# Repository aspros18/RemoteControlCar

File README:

Git URL: https://github.com/fzoli/RemoteControlCar

Bevezetés
---------

A projekt célja egy távirányítós autó vezérlése interneten át.

Az autó vezérlése Android operációs rendszerrel futó mobiltelefon segítségével valósul meg.

A telefon felhasznált eszközkészlete:
- hátsó kamera, ami segítségével lehet látni, mi van az autó előtt
- giroszkóp, ami segítségével meg lehet tudni a gyorsulás és kanyarodás mértékét valamint az út lejtését (ha nincs fék az autón, az emelkedő/lejtő adat alapján megoldható, hogy egy helyben álljon az autó bármikor, ha azt akarjuk)
- GPS vevőt, ami segítségével megbecsülhető a pillanatnyi sebesség és megtudható a kellően pontos tartózkodási hely
- USB port, ami segítségével - egy SparkFun által gyártott mikrovezérlő - az IOIO for Android (DEV-10748) köthető össze a telefonnal. A mikrovezérlőhöz tartozik egy Java nyelvre írt API, ami segítségével ADB (Android Debug Bridge) vagy ADK (Accessory Development Kit) kapcsolaton keresztül a telefon képes kommunikálni a külvilággal. Az API automatikusan kapcsolódik az eszközhöz, nem fontos, melyik kapcsolaton keresztül, de az ADB van előnyben részesítve.
- mobilhálózat, ami segítségével HSPA vagy 3G mobilinternetet használva elküldhető a videó jel, a statisztika és foghatóak a vezérlő jelek
- mobilakku, ami ellátja a mobiltelefont árammal. Azt is jó látni interneten keresztül, hány %-on áll az aksi.

A mikrovezérlő célja:
- vezérelni az autót a telefonnal
- az autó akkumulátorának töltöttségi szintjének megszerzése

Egyéb eszközök:
- kézzel állítható, kétállású kapcsoló, ami eldönti, hogy a beépített mikrovezérlő (ami a gyári távirányító jelének segítségével vezérli az autót) vagy a telefon mikrovezérlője (ami az internetről kapott utasításokkal vezérli az autót) legyen aktív. Erre azért van szükség, hogy ne történhessen meg az, hogy mindkét mikrovezérlő egyazon időben jelzést adjon le és túlfeszültséget okozzon az autó áramkörében
- a lista még bővülni fog olyan dolgokkal mint pl. ellenállás

A hálózati kommunikáció terve:
------------------------------

A kommunikáció SSL titkosítást használva socketek segítségével történik.
A tanúsítványokban szereplő CN (Common Name) mező alapján történik a felhasználó számítógépek és emberek azonosítása, tehát nincsenek felhasználónevek és jelszavak.
Az összes tanúsítvány egyetlen kiállítótól (CA) származik és mind a socket szerver, mind a socket kliensek csakis ebben az egy kiállítóban bízik meg.
Ez azt eredményezi, hogy az összes olyan tanúsítványt elfogadják, amiket a konkrét CA állított ki, de az összes többit elutasítják.

Az SSL többféle próbának is aláveti a socketeket mielőtt létrejönne a kapcsolat:
- megnézi, hogy megbízható-e a tanúsítvány (vagyis inkább a CA)
- megnézi, hogy nem járt-e le a tanúsítvány
- ellenőrzi a hostnevet

A hostnév-ellenőrzés ki van kapcsolva, mert a szabvány szerint a szerver hostnevének és a tanúsítványában szereplő CA mezőnek meg kell egyeznie.
Fentebb írtam, hogy a CA mezőt én a felhasználók azonosítására használom (amolyan felhasználónév szerűség), másrészt a szervernek nem feltétlenül van hostneve vagy a hostnév változó (Pl. IP cím alapján is lehet szerverhez kapcsolódni).

Az egyszerűsített kapcsolati ábra:
Host <-> Bridge <*> Controller

Jelmagyarázat:
<-> egy-egy kapcsolat
<*> egy-sok kapcsolat
Host: a mobiltelefon által indított kliens socket (magyarban is host)
Bridge: egy olyan socket szerver, ami kliens socketek kapcsolódására vár (magyarra fordítva: híd)
Controller: azok a kliens programok, amik segítségével vezérelhető az autó (magyarra fordítva: vezérlő)

Host:
-----

Socket oldalról megközelítve:
A host az én esetemben egy mobiltelefon, ami legtöbbször mobilinternetet - ritkábban Wi-Fi hálózatot és akkor belső IP alapján is lehet címezni - használ  arra, hogy fel tudja venni a kapcsolatot a híddal. Socket szempontjából ő kliens szerepet tölt be. Ennek az az oka, hogy az összes internetes IPv4 cím ki lett már osztva és az internetszolgáltatók minden trükköt bevetnek, hogy ki tudják szolgálni az összes internetet használni akaró gépet. A mobilszolgáltatók ezért NAT-olt IP címet osztanak ki a mobilinternetet használó gépeknek. Ezzel a trükkel egy internetes IP cím (rövidebben WAN IP) több géphez is tartozhat, tehát több gépet ki lehet szolgálni, de van egy hátránya is - amiről a mobilinternetezők nagy része nem is tud - mégpedig az, hogy nincs egy elérhető aktív port sem. Mivel nincs aktív port, hiába üzemeltetünk szervert a telefonon, azt az internetről nem lehet elérni, vagyis csak kliens szerep lehetséges.

A kamera elérése:
A telefon kamerájának képkockái MJPEG streameléssel jutnak el a hídhoz.
Eredeti elképzelésem szerint saját magam olvastam volna a kamera képét és küldtem volna a socket servernek.
A probléma ott kezdődött, hogy az android API nem éppen programozóbarát ha médiáról van szó.
Egyrészt csak akkor hajlandó képkockákat adni, ha azt felületen is megjelenítem (és ennek nem sok értelme van) valamint az eseménykezelőben egy bájt tömböt kapok, amiben YUV formátumú kép van. Ezzel még nem is lenne gond, mert ha valakinek csak a fekete-fehér tartomány kell, akkor még örül is neki, de ha színes képet szeretne az én telefonom kb. 800 ezredmásodpercig dolgozik rajta és akkor még nem is méreteztem át, nem is tömörítettem JPEG formátumba. Olyan 0.7 FPS érhető el így összességében. Gondoltam utánanézek már kész androidos programoknak, amik tudnak videót streamelni. A sok androidos program közül egy megfelelően működőt találtam is, aminek a neve IP Webcam. Java csomag alapján keresve "com.pas.webcam". Ez volt az egyetlen olyan program, ami már megfelelő FPS-t tudott és nem észleltem késést sem. Meg is néztem az okát (hogy hogyan, az már más kérdés). Natív kódot használtak fel, amit C nyelven írtak meg. (Az Android is támogatja a natív kódokat. Bővebben: NDK - Native Development Kit)
Az IP Webcam program HTTP szervert használ és lehetőség van felhasználónév és jelszó beállítására, valamint megadhatjuk a szerver portját, a JPEG képek paramétereit (felbontás, FPS, képminőség) és hogy induljon-e el a telefon indulásakor a program, hogy bármikor hozzá lehessen férni a kamerához.

A telefonon futó program terve:
A telefonon egy Android service fog futni, amit egy egyszerű Activity felületről lehet majd elindítani ill. leállítani.
A service ha leállítódik valami ok miatt (pl. kevés a memória), úgy lesz beállítva, hogy amint lehetséges, induljon el.
Ha a telefon újraindulna miközben a service fut (pl. SD kártyáról fut vagy 100 program és szegény kártya nem bírja olyan gyorsan adni az adatokat mint kéne), a service az OS (operációs rendszer rövidítése) felállása után szintén elindul.
A service az elindulása után azonnal kapcsolódni próbál a hídhoz, ha nem sikerül percenként próbálkozik.
Ha a kapcsolat megszakad, azonnal elindul a kapcsolódás folyamata.
Ezzel minden nem várt hibára megtörtént az óvintézkedés.
A service elindulásakor, ha nem fut az IP Webcam program, akkor az API-ja segítségével a service elindítja azt. (Az ip-webcam könyvtárban további infó.)
A service elindítása előtt a felületen a menüből kezdeményezhető további beállítás.
Itt kell megadni:
- a híd címét (host vagy IP) és portját (amin a socket servlet figyel)
- a tanúsítvány publikus kulcsát (crt fájl) és privát kulcsát (key fájl), amivel a hídhoz kapcsolódik és titkosít.
- a tanúsítvány kiállítójának publikus kulcsát
- mennyi időközönként küldjön statisztikát a telefon
Opcionális beállításként megadható a híd tanúsítványának CN mezője, csak a biztonság kedvéért.
Előfordulhat, hogy rossz címet állítottunk be és nem a híd van címezve. Ez esetben ha a CN mező meg van adva, kiküszöbölhető a fölösleges kapcsolódás és azonnal egyértelmű hibajelzést kapunk. Ha nincs megadva a CN mező, a program percenként fölöslegesen fog próbálkozni, konkrét hibát nem jelezve.

A hang stream, eredetileg kikapcsolt és kérhető lesz bekapcsolásra. Kikapcsolása esetén elég a socket streamet lezárni és kezelni kell a kivételt.
A streamet az android beépített szolgáltatása (MediaRecorder.AudioEncoder.AAC) fogja szolgáltatni és a híd fogja tovább adni a vezérlőknek.

Bridge:
-------

A hídnak két szerepköre van:
- vár a hostra - amitől a videót és a statisztikát kapja és akinek a vezérlőjelet küldi majd
- kiszolgálja a vezérlőket - amik irányítani szeretnék az autót - és eldönti, hogy ki vezérelheti az autót, ha több kérés van egy időben

Úgy terveztem meg a socket alapú kommunikációkat, hogy a híd el tudja dönteni, mi célja lesz a kapcsolatnak és egy időben több kapcsolatot kezelhessen.
A híd esetén a host CN mezőjét kötelező megadni, mert a híd ez alapján tudja, hogy a socket kliens vezérlő-e vagy host. EZ NAGYON FONTOS!!!
A híd esetében megadható több CN mező is, amik segítségével lehet tudni, mely tanúsítványok lesznek a hostok ha esetleg több autó is távvezérelt lesz a jövőben. (Meg lehetett volna oldani úgy is, hogy a socket kliensek még a kapcsolatazonosító kérése előtt közölték volna, hogy ők hostok vagy vezérlők, de ez esetben a híd nem tudna pontos listát adni a hostokról.)

[Opcionális terv: A híd mellé lehetne egy webszervert is tenni. Regisztrálhatnának internetről mások, akiknek el lett adva egy ilyen autó és van hozzá mobiltelefonjuk. A webszerver is SSL-t használna az alapértelmezett 443-as porttal. Itt akár tanúsítványt is generáltathatnának (hostjukhoz és vezérlőjeikhez) így a híd socket servere megbízhatónak találná őket és szintén tudná ki a host és ki a vezérlő. A híd szolgáltatása havidíjas is lehetne és azoknak lenne jó, akik nem szeretnének saját híd szervert üzemeltetni. A host mikrovezérlő kódját ez esetben úgy kellene megtervezni, hogy interface alapú legyen és a felületről több autó típust lehessen választani az implementált osztályok alapján. Szép álom lenne, ha a mobilinternetes szolgáltatókkal meg lehetne egyezni, hogy ne mérjék a forgalmat és kapnak a bevételből :-) ]

Host felőli kapcsolatok:
1. MJPEG stream: hídnak letöltés, hostnak feltöltés
2. Statisztika adatok: objektumos stream, hídnak letöltés, hostnak feltöltés
3. Vezérlő parancsok a hídtól (az autónak és a telefonon futó programnak): objektumos stream, hídnak feltöltés, hostnak letöltés

Vezérlő felőli kapcsolatok:
1. MJPEG stream: hídnak feltöltés, vezérlőnek letöltés
2. Statisztika adatok (a hostról és a hídról): objektumos stream, hídnak feltöltés, vezérlőnek letöltés
3. Vezérlő parancsok a vezérlőtől (a hostnak és a hídnak): objektumos stream, hídnak letöltés, vezérlőnek feltöltés

Bővebb magyarázat:
- A kapcsolatok előtt a számozás kapcsolatazonosítót és prioritási sorrendet is jelent.
- A híd a hostnak főként autóvezérlő utasításokat közöl (a 3-mas kapcsolaton át), de a telefonnak közölheti azt is,
  hogy hagyja abba az MJPEG streamelést vagy éppen kezdje el.
- A vezérlő a hídnak főként autóvezérlő utasításokat ad, de üzenhet a hídnak is, hogy szeretné átvenni az autó irányítását.
- A híd is üzenhet a vezérlőnek, ha éppen elvették tőle az irányítást, jelezze a felületen.

A kapcsolat kialakítása a következő módon valósul meg:
A kliens három kapcsolatot alakít ki ugyan azzal a sockettel, a kapcsolat létrejötte után új szálban kezdődik meg a feldolgozás.
A szerver amíg aktívan fut (tehát a Socket server nincs bezárva) cikluson belül mindig várja a klienseket és ha létrejön egy SSLSocket, ő is külön szálban dolgozik vele tovább, hogy képes legyen több kapcsolatot kiszolgálni egy időben.

A kapcsolat kialakításának lépései: (Szerver alatt a híd socket szerverét értem.)
0. A kliens socket kapcsolódik a szerver sockethez és sikerül az SSL kézfogás, létrejön a kapcsolat és mindkét oldalon egy SSLSocket objektum.
1. a) A szerver a kliens-tanúsítvány CN mezejének alapján megtudja, hogy a kliens host vagy vezérlő és hogy pontosan kivel is van dolga.
   b) A szerver megnézi, hogy az adott szerepkörben az adott névhez hány kapcsolat van már kialakítva.
   c) A szerver inkrementálja a B pontban kapott számot és így megkapja az aktuális kapcsolat azonosítóját
      és a fenti felsorolás alapján már tudja is, mire lesz használva a kapcsolat.
2. A szerver elküldi a kliensnek a kapcsolatazonosítót. Másképp fogalmazva: A kliens lekéri a kapcsolatazonosítót.
3. Mindkét oldal a kapcsolatazonosító alapján együttműködve kezeli a kapcsolatot.
4. Bármelyik oldal lezárhatja a kapcsolatot, ha úgy dönt. Ekkor befejeződik a kommunikáció.

Ha a hídra ugyan azzal a tanúsítvánnyal kapcsolódnak több helyről, a híd a régebbi kapcsolatokat bezárja.
Így ki van kerülve az, hogy két helyről vezérelhessék az autót ellentmondásos üzenetet leadva mint pl. menj jobbra és balra is.

Jogkezelés:
Előfordulhat olyan eset, hogy egy autót több vezérlő is szeretne irányítani.
Erre azt találtam ki, hogy csinálok a hídra egy tanúsítvány-prioritás listát.
A nagyobb prioritású vezérlő bármikor elveheti a vezérlést a kisebb prioritású vezérlőktől, de egyébként minden vezérlő kapcsolódhat a hídhoz és minden
információt láthat, csak a vezérléstől vannak megfosztva.
Amint felszabadul a vezérlés, bárki kérheti az autó vezérlését prioritástól függetlenül és meg is kapja.
(Kérni lehet akkor is, ha éppen vezérlik az autót, de az csak kérvényt jelent, semmi többet. Amint felszabadul a vezérlés az első kérvényt benyújtó meg is kapja.)
(Ha a prioritáslistában egyetlen név szerepel, akkor úgy fog funkcionálni, mint ha root lenne, mivel mindenki felett áll ez esetben.)
Ha nagyobb prioritású kapcsolódik a hídhoz, mint aki vezérli az autót, addig amíg nem kéri a vezérlést, nem veszi el a híd az aktuális vezérlőtől az irányítást.
Aki nem szerepel a prioritáslistában, az olyan, mint ha a legutolsó utolsó helyen szerepelne a listában és a többi - listában nem szereplő - felhasználóval egyenrangúnak számít, tehát ők egymástól nem tudják elvenni a vezérlést.
Ha a vezérlő sokáig nem cselekszik, tehát nincs a gép előtt, a vezérlést elveszi a híd tőle.

Internet sávszélesség:
A híd létrejöttének fő célja az volt, hogy egyetlen egy kapcsolat (ami valójában három socket kapcsolat) legyen a mobilinternet oldaláról és az is takarékos legyen mivel forgalom- és sebességkorlátos az internet.
A hídba be van téve egy olyan sávszélesség csökkentő funkció is, hogy csak akkor kéri az MJPEG streamet a hosttól, ha van legalább egy vezérlő kapcsolódva hozzá.

Konfig fájl:
A híd esetén is meg kell adni a tanúsítvány publikus és titkos kulcsának az elérhetőségét és a kiállító publikus kulcsának az elérhetőségét.
A tanúsítvány prioritásokat és a hostlistát is itt kell megadni, de ha bevezetésre kerül egy webes felület, átkerülnek egy közös adatbázisba.

Controller:
-----------

A vezérlő az a program, ami megjeleníti az autó adatait és ha van lehetősége vezérli az autót.
Ez egy PC-n futó java alapú desktop alkalmazás lényegében, ami szintén a hídhoz kapcsolódik socket kliensként.
A felületen lehetőség van - és kötelező is első induláskor - beállítani a híd címét és portját valamint a tanúsítvány publikus és titkos kulcsát és a kiállító publikus kulcsát.
A kiállító kulcsára azért van szükség mert kliens oldalon is ellenőrizve van a szerver tanúsítvány megbízhatósága, nem csak szerver oldalon, hogy a man-in-middle támadás lehetetlen legyen.
A vezérlés billentyűzet és egér segítségével történik.
Az egérrel pontos utasítást lehet adni mind sebesség, mind irány terén.
A billentyűzettel egyszerűbb, de durvább irányítást érhet el a felhasználó és több vezérlés mód közül választhat.
(A vezérlési módok a durvaságot szabályozzák pl. előre nyílra egyenletesen gyorsuljon fel vagy földkaparással max grafttal induljon el)

Egy kis trükk:
--------------

Egyes mobilszolgáltatók csomagjaiban a webböngészés nem számít bele a forgalomkorlátba.

Ez esetben socketek helyett mondjuk Tomcat webszervert lehetne használni.
- A terv lényege ugyan az, csak a kapcsolatazonosítók helyett HTTP címzés lenne használva.
- Az MJPEG stream HTTP POST-tal streamelhető a hídnak - ami a Tomcat webszerver.
- A vezérlő utasítások JSON-nal objektummá alakíthatók Stringből és objektumból Stringre, és a HTTP tartalom is gond nélkül használható streamelés céljára.

Továbbfejlesztés
----------------

További két socket kapcsolat segítségével megoldható lenne, hogy a telefon mikrofonjából megkapjuk a hangot is a kép mellé és a vezérlő számítógép mikrofonjából meg a telefonon játsszunk le hangot.
A telefonból érkező hang stream ki/be kapcsolható lenne, alapértelmezetten ki lenne kapcsolva takarékosság miatt.
Az autót vezérlő kliens tudná csak ki/be kapcsolni a streamet és csakis ő tudna hang streamet küldeni a telefonnak.
A sávszélesség kímélése érdekében a Javara írt Tritonus API-t használva lehetne tömöríteni GSM vagy MP3 formátumba a monó 16 bites PCM-ről. (Mondjuk GSMFormatConversionProvider segítségével.)
Egyéb pluginok: http://www.tritonus.org/plugins.html
Példa: http://www.jsresources.org/examples/GSMEncoder.java.html
Ha a Tritonus még sem használható út, marad a GZipInputStream és társa a GZipOutputStream.
Vagy egy másik út: http://www.jsresources.org/apps/9159_TimeTurner.pdf

Az autón lévő tartó, amiben a mobil lesz, lehetne motor által vezérelhető, hogy a kereszteződéseket be lehessen látni és igény szerint hátra is lehessen tekinteni.
A giroszkóp adatait a telefon programja csak az alapállásban adná le a megbízhatóság miatt. (Vagy ha szükség van rá, akkor csak a motor mozgása közben lenne inaktív és az algoritmus meg lenne írva úgy, hogy több helyzetből is jó adatokat közöljön.)

A telefont tartó eszköz lehetőleg védje a telefont a külső támadások ellen és az eső ellen, kulccsal zárható legyen.
Ha ez meg lett oldva, a kábeleket is jó lenne biztonságosan elvezetni szintén védve és a kapcsolót, ami átkapcsolhat internetes vezérlésről, azt is a kulccsal
zárt, védett helyen belülre kéne elhelyezni.

Nem ártana egy közös chat funkció se. Nem kellene tárolni az üzeneteket, ebből kifolyólag nem lenne offline üzenetküldés.
Csak annyi célja lenne, hogy az autót vezérlő felhasználók tudjanak beszélgetni egymással.

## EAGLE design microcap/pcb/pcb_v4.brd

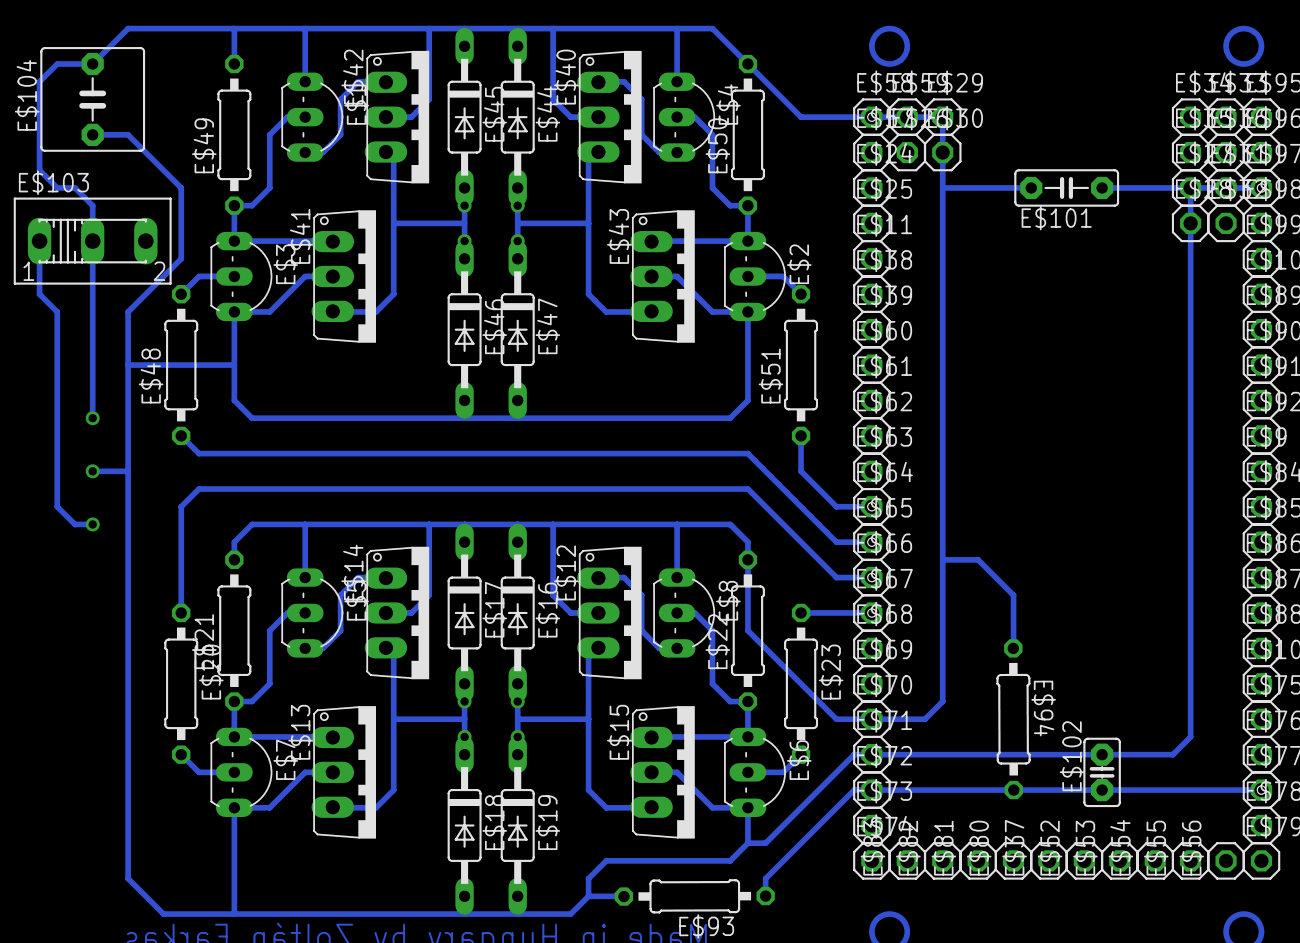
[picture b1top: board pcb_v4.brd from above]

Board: 2 copper layers, 104 parts (0 on the bottom side), 18 nets.

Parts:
E$1, E$2, E$3, E$4, E$5, E$6, E$7, E$8: TO92-CBE
E$9, E$10, E$11, E$24, E$25, E$26, E$27, E$28, E$29, E$30, E$31, E$32, E$33, E$34, E$35, E$36, E$37, E$38, E$39, E$52, E$53, E$54, E$55, E$56, E$57, E$58, E$59, E$60, E$61, E$62, E$63, E$64, E$65, E$66, E$67, E$68, E$69, E$70, E$71, E$72, E$73, E$74, E$75, E$76, E$77, E$78, E$79, E$80, E$81, E$82, E$83, E$84, E$85, E$86, E$87, E$88, E$89, E$90, E$91, E$92, E$95, E$96, E$97, E$98, E$99, E$100: 1X01
E$12, E$13, E$14, E$15, E$40, E$41, E$42, E$43: T-30_V
E$16, E$17, E$18, E$19, E$44, E$45, E$46, E$47: C2992
E$20, E$21, E$22, E$23, E$48, E$49, E$50, E$51, E$93, E$94: 0207/10
E$101: C5B2.5
E$102: C2.5-2
E$103: 255SB
E$104: C5B7.2

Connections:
S$2: E$2.C, E$4.B, E$50.1
S$5: E$3.B, E$48.2
S$6: E$2.B, E$51.2
S$7: E$5.B, E$7.C, E$21.1
S$8: E$45.A, E$46.C
S$9: E$1.B, E$3.C, E$49.1
S$12: E$17.A, E$18.C
S$15: E$23.1, E$67.1
S$16: E$6.C, E$8.B, E$22.1
S$17: E$6.B, E$23.2
S$18: E$51.1, E$64.1
S$19: E$16.A, E$19.C
S$21: E$7.B, E$20.2
S$22: E$44.A, E$47.C
S$23: E$48.1, E$65.1
S$28: E$1.C, E$4.C, E$5.C, E$8.C, E$16.C, E$17.C, E$21.2, E$22.2, E$29.1, E$44.C, E$45.C, E$49.2, E$50.2, E$58.1, E$59.1, E$70.1, E$101.2, E$103.2, E$104.2
S$29: E$2.E, E$3.E, E$6.E, E$7.E, E$18.A, E$19.A, E$46.A, E$47.A, E$71.1, E$97.1, E$101.1, E$104.1
S$36: E$20.1, E$66.1

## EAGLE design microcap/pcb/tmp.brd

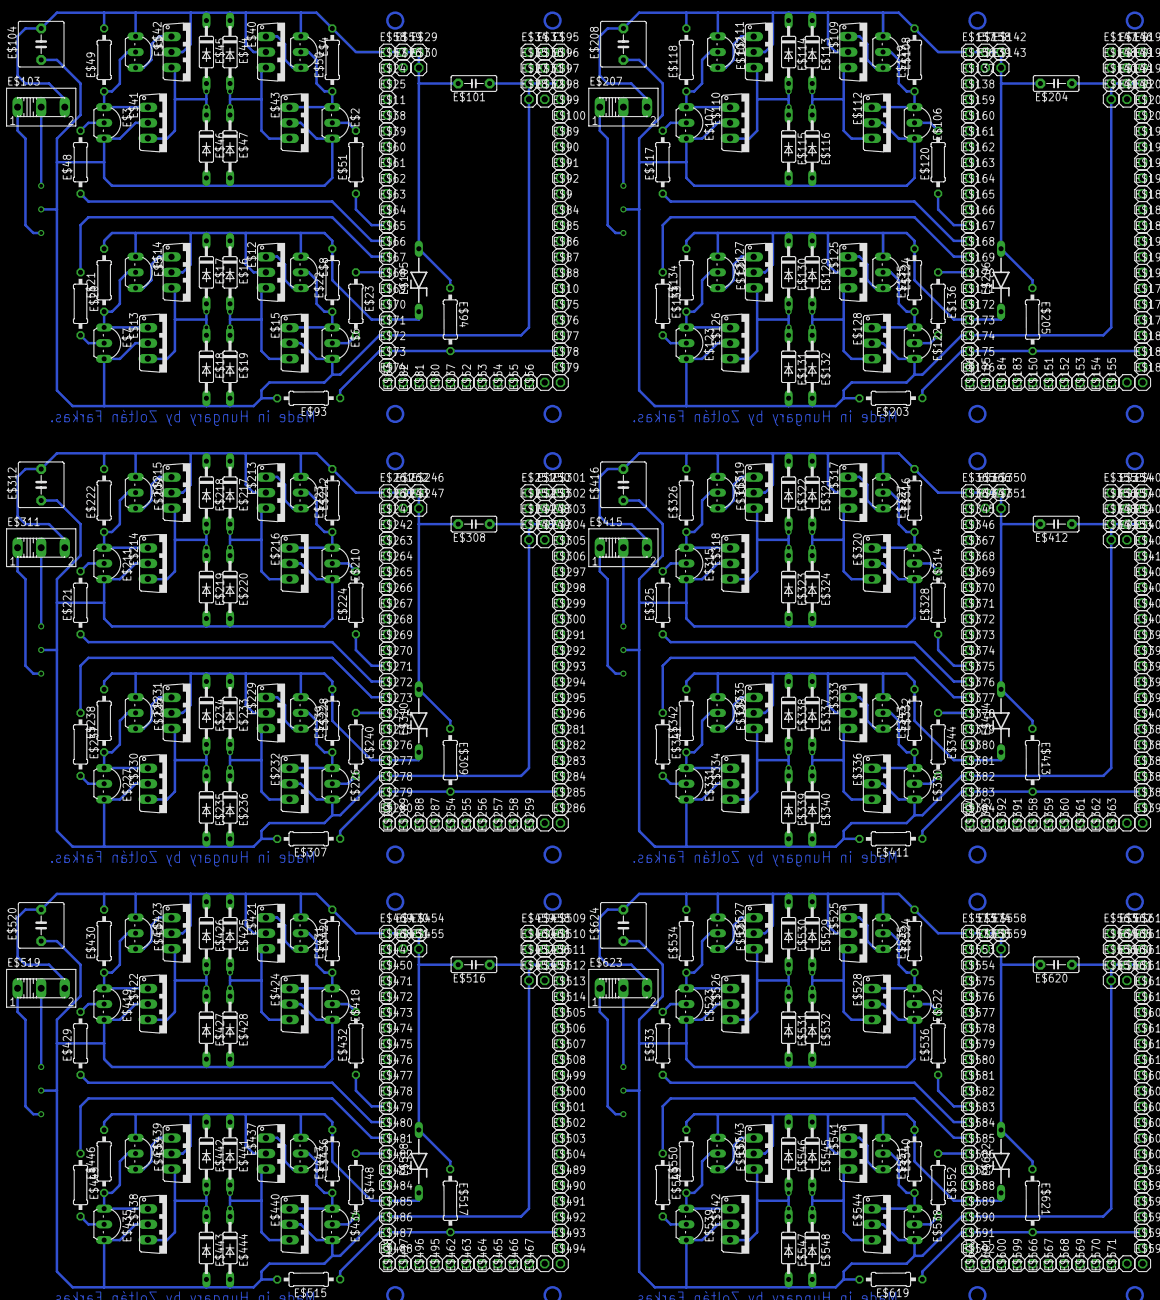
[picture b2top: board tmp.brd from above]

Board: 2 copper layers, 624 parts (0 on the bottom side), 114 nets.

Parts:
E$1, E$2, E$3, E$4, E$5, E$6, E$7, E$8, E$102, E$106, E$107, E$108, E$121, E$122, E$123, E$124, E$209, E$210, E$211, E$212, E$225, E$226, E$227, E$228, E$313, E$314, E$315, E$316, E$329, E$330, E$331, E$332, E$417, E$418, E$419, E$420, E$433, E$434, E$435, E$436, E$521, E$522, E$523, E$524, E$537, E$538, E$539, E$540: TO92-CBE
E$9, E$10, E$11, E$24, E$25, E$26, E$27, E$28, E$29, E$30, E$31, E$32, E$33, E$34, E$35, E$36, E$37, E$38, E$39, E$52, E$53, E$54, E$55, E$56, E$57, E$58, E$59, E$60, E$61, E$62, E$63, E$64, E$65, E$66, E$67, E$68, E$69, E$70, E$71, E$72, E$73, E$74, E$75, E$76, E$77, E$78, E$79, E$80, E$81, E$82, E$83, E$84, E$85, E$86, E$87, E$88, E$89, E$90, E$91, E$92, E$95, E$96, E$97, E$98, E$99, E$100, E$137, E$138, E$139, E$140, E$141, E$142, E$143, E$144, E$145, E$146, E$147, E$148, E$149, E$150, E$151, E$152, E$153, E$154, E$155, E$156, E$157, E$158, E$159, E$160, E$161, E$162, E$163, E$164, E$165, E$166, E$167, E$168, E$169, E$170, E$171, E$172, E$173, E$174, E$175, E$176, E$177, E$178, E$179, E$180, E$181, E$182, E$183, E$184, E$185, E$186, E$187, E$188, E$189, E$190, E$191, E$192, E$193, E$194, E$195, E$196, E$197, E$198, E$199, E$200, E$201, E$202, E$241, E$242, E$243, E$244, E$245, E$246, E$247, E$248, E$249, E$250, E$251, E$252, E$253, E$254, E$255, E$256, E$257, E$258, E$259, E$260, E$261, E$262, E$263, E$264, E$265, E$266, E$267, E$268, E$269, E$270, E$271, E$272, E$273, E$274, E$275, E$276, E$277, E$278, E$279, E$280, E$281, E$282, E$283, E$284, E$285, E$286, E$287, E$288, E$289, E$290, E$291, E$292, E$293, E$294, E$295, E$296, E$297, E$298, E$299, E$300, E$301, E$302, E$303, E$304, E$305, E$306, E$345, E$346, E$347, E$348, E$349, E$350, E$351, E$352, E$353, E$354, E$355, E$356, E$357, E$358, E$359, E$360, E$361, E$362, E$363, E$364, E$365, E$366, E$367, E$368, E$369, E$370, E$371, E$372, E$373, E$374, E$375, E$376, E$377, E$378, E$379, E$380, E$381, E$382, E$383, E$384, E$385, E$386, E$387, E$388, E$389, E$390, E$391, E$392, E$393, E$394, E$395, E$396, E$397, E$398, E$399, E$400, E$401, E$402, E$403, E$404, E$405, E$406, E$407, E$408, E$409, E$410, E$449, E$450, E$451, E$452, E$453, E$454, E$455, E$456, E$457, E$458, E$459, E$460, E$461, E$462, E$463, E$464, E$465, E$466, E$467, E$468, E$469, E$470, E$471, E$472, E$473, E$474, E$475, E$476, E$477, E$478, E$479, E$480, E$481, E$482, E$483, E$484, E$485, E$486, E$487, E$488, E$489, E$490, E$491, E$492, E$493, E$494, E$495, E$496, E$497, E$498, E$499, E$500, E$501, E$502, E$503, E$504, E$505, E$506, E$507, E$508, E$509, E$510, E$511, E$512, E$513, E$514, E$553, E$554, E$555, E$556, E$557, E$558, E$559, E$560, E$561, E$562, E$563, E$564, E$565, E$566, E$567, E$568, E$569, E$570, E$571, E$572, E$573, E$574, E$575, E$576, E$577, E$578, E$579, E$580, E$581, E$582, E$583, E$584, E$585, E$586, E$587, E$588, E$589, E$590, E$591, E$592, E$593, E$594, E$595, E$596, E$597, E$598, E$599, E$600, E$601, E$602, E$603, E$604, E$605, E$606, E$607, E$608, E$609, E$610, E$611, E$612, E$613, E$614, E$615, E$616, E$617, E$618: 1X01
E$12, E$13, E$14, E$15, E$40, E$41, E$42, E$43, E$109, E$110, E$111, E$112, E$125, E$126, E$127, E$128, E$213, E$214, E$215, E$216, E$229, E$230, E$231, E$232, E$317, E$318, E$319, E$320, E$333, E$334, E$335, E$336, E$421, E$422, E$423, E$424, E$437, E$438, E$439, E$440, E$525, E$526, E$527, E$528, E$541, E$542, E$543, E$544: T-30_V
E$16, E$17, E$18, E$19, E$44, E$45, E$46, E$47, E$113, E$114, E$115, E$116, E$129, E$130, E$131, E$132, E$217, E$218, E$219, E$220, E$233, E$234, E$235, E$236, E$321, E$322, E$323, E$324, E$337, E$338, E$339, E$340, E$425, E$426, E$427, E$428, E$441, E$442, E$443, E$444, E$529, E$530, E$531, E$532, E$545, E$546, E$547, E$548: C2992
E$20, E$21, E$22, E$23, E$48, E$49, E$50, E$51, E$93, E$94, E$117, E$118, E$119, E$120, E$133, E$134, E$135, E$136, E$203, E$205, E$221, E$222, E$223, E$224, E$237, E$238, E$239, E$240, E$307, E$309, E$325, E$326, E$327, E$328, E$341, E$342, E$343, E$344, E$411, E$413, E$429, E$430, E$431, E$432, E$445, E$446, E$447, E$448, E$515, E$517, E$533, E$534, E$535, E$536, E$549, E$550, E$551, E$552, E$619, E$621: 0207/10
E$101, E$204, E$308, E$412, E$516, E$620: C5B2.5
E$103, E$207, E$311, E$415, E$519, E$623: 255SB
E$104, E$208, E$312, E$416, E$520, E$624: C5B7.2
E$105, E$206, E$310, E$414, E$518, E$622: ZDIO-10

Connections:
S$2: E$2.C, E$4.B, E$50.1
S$5: E$3.B, E$48.2
S$6: E$2.B, E$51.2
S$7: E$5.B, E$7.C, E$21.1
S$8: E$45.A, E$46.C
S$9: E$1.B, E$3.C, E$49.1
S$12: E$17.A, E$18.C
S$15: E$23.1, E$67.1
S$16: E$6.C, E$8.B, E$22.1
S$17: E$6.B, E$23.2
S$18: E$51.1, E$64.1
S$19: E$16.A, E$19.C
S$21: E$7.B, E$20.2
S$22: E$44.A, E$47.C
S$23: E$48.1, E$65.1
S$25: E$1.C, E$4.C, E$29.1, E$44.C, E$45.C, E$49.2, E$50.2, E$58.1, E$59.1, E$101.2, E$103.3, E$104.2
S$28: E$5.C, E$8.C, E$16.C, E$17.C, E$21.2, E$22.2, E$70.1, E$105.C
S$29: E$2.E, E$3.E, E$6.E, E$7.E, E$18.A, E$19.A, E$46.A, E$47.A, E$71.1, E$97.1, E$101.1, E$104.1
S$33: E$102.B, E$107.C, E$118.1
S$36: E$20.1, E$66.1
S$37: E$106.C, E$108.B, E$119.1
S$40: E$121.B, E$123.C, E$134.1
S$43: E$122.C, E$124.B, E$135.1
S$44: E$130.A, E$131.C
S$45: E$129.A, E$132.C
S$46: E$133.1, E$168.1
S$47: E$120.1, E$166.1
S$48: E$117.1, E$167.1
S$51: E$114.A, E$115.C
S$52: E$113.A, E$116.C
S$53: E$121.C, E$124.C, E$129.C, E$130.C, E$134.2, E$135.2, E$172.1, E$206.C
S$54: E$136.1, E$169.1
S$55: E$107.B, E$117.2
S$56: E$106.B, E$120.2
S$57: E$122.B, E$136.2
S$58: E$123.B, E$133.2
S$59: E$106.E, E$107.E, E$115.A, E$116.A, E$122.E, E$123.E, E$131.A, E$132.A, E$173.1, E$199.1, E$204.1, E$208.1
S$61: E$102.C, E$108.C, E$113.C, E$114.C, E$118.2, E$119.2, E$142.1, E$157.1, E$158.1, E$204.2, E$207.3, E$208.2
S$65: E$209.B, E$211.C, E$222.1
S$68: E$210.C, E$212.B, E$223.1
S$71: E$225.B, E$227.C, E$238.1
S$74: E$226.C, E$228.B, E$239.1
S$75: E$234.A, E$235.C
S$76: E$233.A, E$236.C
S$77: E$237.1, E$272.1
S$78: E$224.1, E$270.1
S$79: E$221.1, E$271.1
S$82: E$218.A, E$219.C
S$83: E$217.A, E$220.C
S$84: E$225.C, E$228.C, E$233.C, E$234.C, E$238.2, E$239.2, E$276.1, E$310.C
S$85: E$240.1, E$273.1
S$86: E$211.B, E$221.2
S$87: E$210.B, E$224.2
S$88: E$226.B, E$240.2
S$89: E$227.B, E$237.2
S$90: E$210.E, E$211.E, E$219.A, E$220.A, E$226.E, E$227.E, E$235.A, E$236.A, E$277.1, E$303.1, E$308.1, E$312.1
S$92: E$209.C, E$212.C, E$217.C, E$218.C, E$222.2, E$223.2, E$246.1, E$261.1, E$262.1, E$308.2, E$311.3, E$312.2
S$96: E$313.B, E$315.C, E$326.1
S$99: E$314.C, E$316.B, E$327.1
S$102: E$329.B, E$331.C, E$342.1
S$105: E$330.C, E$332.B, E$343.1
S$106: E$338.A, E$339.C
S$107: E$337.A, E$340.C
S$108: E$341.1, E$376.1
S$109: E$328.1, E$374.1
S$110: E$325.1, E$375.1
S$113: E$322.A, E$323.C
S$114: E$321.A, E$324.C
S$115: E$329.C, E$332.C, E$337.C, E$338.C, E$342.2, E$343.2, E$380.1, E$414.C
S$116: E$344.1, E$377.1
S$117: E$315.B, E$325.2
S$118: E$314.B, E$328.2
S$119: E$330.B, E$344.2
S$120: E$331.B, E$341.2
S$121: E$314.E, E$315.E, E$323.A, E$324.A, E$330.E, E$331.E, E$339.A, E$340.A, E$381.1, E$407.1, E$412.1, E$416.1
S$123: E$313.C, E$316.C, E$321.C, E$322.C, E$326.2, E$327.2, E$350.1, E$365.1, E$366.1, E$412.2, E$415.3, E$416.2
S$127: E$417.B, E$419.C, E$430.1
S$130: E$418.C, E$420.B, E$431.1
S$133: E$433.B, E$435.C, E$446.1
S$136: E$434.C, E$436.B, E$447.1
S$137: E$442.A, E$443.C
S$138: E$441.A, E$444.C
S$139: E$445.1, E$480.1
S$140: E$432.1, E$478.1
S$141: E$429.1, E$479.1
S$144: E$426.A, E$427.C
S$145: E$425.A, E$428.C
S$146: E$433.C, E$436.C, E$441.C, E$442.C, E$446.2, E$447.2, E$484.1, E$518.C
S$147: E$448.1, E$481.1
S$148: E$419.B, E$429.2
S$149: E$418.B, E$432.2
S$150: E$434.B, E$448.2
S$151: E$435.B, E$445.2
S$152: E$418.E, E$419.E, E$427.A, E$428.A, E$434.E, E$435.E, E$443.A, E$444.A, E$485.1, E$511.1, E$516.1, E$520.1
S$154: E$417.C, E$420.C, E$425.C, E$426.C, E$430.2, E$431.2, E$454.1, E$469.1, E$470.1, E$516.2, E$519.3, E$520.2
S$158: E$521.B, E$523.C, E$534.1
S$161: E$522.C, E$524.B, E$535.1
S$164: E$537.B, E$539.C, E$550.1
S$167: E$538.C, E$540.B, E$551.1
S$168: E$546.A, E$547.C
S$169: E$545.A, E$548.C
S$170: E$549.1, E$584.1
S$171: E$536.1, E$582.1
S$172: E$533.1, E$583.1
S$175: E$530.A, E$531.C
S$176: E$529.A, E$532.C
S$177: E$537.C, E$540.C, E$545.C, E$546.C, E$550.2, E$551.2, E$588.1, E$622.C
S$178: E$552.1, E$585.1
S$179: E$523.B, E$533.2
S$180: E$522.B, E$536.2
S$181: E$538.B, E$552.2
S$182: E$539.B, E$549.2
S$183: E$522.E, E$523.E, E$531.A, E$532.A, E$538.E, E$539.E, E$547.A, E$548.A, E$589.1, E$615.1, E$620.1, E$624.1
S$185: E$521.C, E$524.C, E$529.C, E$530.C, E$534.2, E$535.2, E$558.1, E$573.1, E$574.1, E$620.2, E$623.3, E$624.2

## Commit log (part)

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2013-03-17 note
2013-03-17 cleaning
2013-03-17 bugfix
2013-03-18 msi installer is created
2013-03-18 mac jarbundler testing
2013-03-23 testing
2013-03-23 application chooser window is added
2013-03-23 app chooser testing
2013-03-24 snapshot
2013-03-24 msi installer update
2013-03-24 outer test
2013-03-25 MSI installer is minimized
2013-03-25 linux-installer is minimized
2013-03-25 text replace
2013-03-25 localizing
2013-03-26 photo update
2013-03-26 setting button is added
2013-03-27 Shell32.dll test
2013-03-27 release update
2013-03-27 app-chooser margin change
2013-03-27 config update
2013-04-01 ui-native.zip
2013-04-05 changeable voltage thresholds
2013-04-05 arrow dialog cursor update
2013-04-05 pcb uploading
2013-04-06 pcb update
2013-04-06 min/max voltage threshold options are added
2013-04-06 sdcard path fix
2013-04-09 dist update
2013-04-10 Mac OS X test
2013-04-11 Mac OS X snapshots
2013-04-15 mac-testing
2013-04-20 ProcessBuilder testing
2013-04-20 mac installer is uploaded
2013-04-21 mac focus-testing
2013-04-22 mac-installer update
2013-04-22 release v1.0.0
2013-04-22 nativeswing test update
2013-04-22 position of about frame is changed
2013-04-23 native Windows release v1.0.0
2013-04-23 release v1.0.0.2 error dialogs display the file path
2013-04-23 release v1.0.1.3 security fix for server side
2013-04-24 release v1.0.2.4 safer reconnection
2013-04-24 release v1.0.2.5 incompatible client version text is relocalized
2013-04-24 release v1.0.2.5 incompatible client version text is relocalized reconnect fix on Android
2013-04-24 release v1.0.2.5 mac-installer is updated native release to Windows
2013-04-25 release v1.0.3.6 on Mac the server starts the process of the client application with "open -n" command
2013-04-25 release v1.0.3.7 magnetic declination is added to the Android code
2013-04-25 release v1.0.3.8 sensor timeout is increased
2013-04-26 release v1.0.3.8 Mac and Windows installers are uploaded
2013-04-26 release v1.0.3.8 Windows native release
2013-05-01 release 1.0.3.9 image icon resizing is changed to balanced from antialias
2013-05-01 release 1.0.3.9
2013-05-01 release 1.0.3.10 on Mac, -W parameter is added to the open command
2013-05-07 release 1.0.3.11 bugfix - AWT Tray Icon size getter
2013-05-07 release 1.0.4.12 code cleaning; it has no effect
2013-05-08 system tray test frame is created
2013-05-13 Menu display listener has been added to the native tray item.
2013-05-20 BJT H Bridge picture has been saved
2013-05-22 BJT H Bridge picture has been edited
2013-05-26 PCB note has been edited
2013-05-26 autorun.ini has been modified; newlines have been set to Windows
2013-05-26 portable zip has been added
2013-05-26 android app release preparation
2013-05-26 snapshot change
2013-05-30 sub-crt test
2013-05-31 android lib refresh
2013-05-31 release v1.0.4.13
2013-05-31 release v1.0.4.13 message position fix for portrait stream
2013-05-31 release v1.0.4.13 MAC Installer has been uploaded
2013-05-31 release v1.0.4.13 Windows Installer has been uploaded
2013-05-31 release v1.0.5.14 - Android service runs foreground in order to prevent the service from killing by OS - Name of the selected vehicle displays in the title of the chat window
2013-06-01 default pcb photo
2013-06-01 release v1.0.6.15 Android service doesn't start when you go to the settings
2013-06-06 linux-installer bugfix
2013-06-06 linux-installer.bsx - self extracting script has been added
2013-06-09 android test project renaming
2013-06-12 compass mode testing
2013-06-12 release v1.1.8.17 compass mode has been added to the map
2013-06-12 release v1.1.9.18 slow map loading is being displayed on Windows
2013-06-28 native tray test
2013-06-28 release v1.1.10.19 client-side MJPEG optimalization
2013-07-25 release v1.1.11.20 new connection error is detected and fixed
2013-07-26 release v1.1.11.20 new connection error is detected and fixed gps enabling is detected after the connection is established disabling gps won't crash the application
2013-07-26 release v1.1.12.21 mjpeg streaming won't stop
2013-07-26 release v1.1.12.21
2013-07-27 release v1.1.13.22 IP webcam reopen if the user close it while streaming Activity reinitalization doesn't cause reconnect IOIO library is updated
2013-07-28 release v1.1.14.23 a rare android service bugfix try
2013-07-28 release v1.1.16.25 a rare android service bugfix try
2013-07-28 error handling on linux (sudo)
2013-07-29 release v1.1.17.26 duplicated connection on android has been fixed
2013-07-29 release v1.1.18.27 duplicated connection on android has been fixed
2013-08-02 release v1.1.19.28 exception handler precision
2013-08-03 release v1.1.19.28 exception handler precision file extension checking on android
2013-08-13 android release v1.2.0.29 ADB Toggle support
2013-08-25 android release v1.2.1.30 Android 4.3 SDK
2013-08-25 thesis.pdf v0.1
2013-08-26 thesis.pdf v0.2
2013-08-27 video upload
2013-08-27 android release v1.2.2.31 PWM40 test
2013-08-28 video subtitles
2013-08-28 video subtitles (latin2 encoding)
2013-08-28 video subtitles (utf-8 encoding)
2013-08-28 autorun
2013-08-28 thesis.pdf v1.0
2013-08-28 installer update
2013-08-28 android release v1.2.3.32
2013-08-29 thesis.pdf v1.1
2013-08-29 thesis.pdf v1.2
2013-08-29 PDF has been removed from MSI
2013-08-29 readme update
2013-08-29 Setup.wxs update
2013-08-29 android release v1.2.4.33 - message display fix (disconnect instead of cause) - IP Webcam closing message has been added
2013-08-30 android release v1.2.5.34 Service checks configuration too onStart() Minimized exception handling in ConnectionHelper
2013-08-30 android release v1.3.0.35 IOIO Bluetooth Lib has been added
2013-08-30 PWM40 test
2013-08-30 android release v1.3.1.36 Config validating before creating connection IP Webcam Activity checking during paused stream
2013-08-31 android release v1.3.2.37 IOIO multiple connection support (beta)
2013-09-01 v1.1.20.29 BridgeHandler shows unknown errors too
2013-09-03 First connection has to be DisconnectProcess
2013-09-04 1000 byte error message limit
2013-09-04 error message limit: 100 byte
2013-09-06 C++ test
2013-09-08 DeviceHandler class
2013-09-09 JSON test
2013-09-09 testconfig update
2013-09-10 android release v1.4.0
2013-09-10 android release v1.4.0 - permission fix - class not found fix
2013-09-11 C++ mjpeg test
2013-09-14 c++ factory test
2013-09-14 c++ message test
2013-09-15 hyphen is allowed in the address
2013-09-15 c++ mjpeg debug
2013-09-16 c++ debug
2013-09-16 c++ data test
2013-09-16 c++ json test
2013-09-21 c++ StorageList
2013-09-23 c++ HostStorage
2013-09-23 c++ ControllerStorage
2013-09-26 c++ bridge test
2013-09-29 c++ SSLSocket bugfix (causes more bugs)
2013-09-29 c++ SSLSocket bugfix
2013-09-29 c++ msg sender bugfix
2013-09-30 c++ msg deserialization bugfix
2014-01-21 CRT Name property support has been added
2014-02-23 cpp code cleaning
2014-02-28 test
